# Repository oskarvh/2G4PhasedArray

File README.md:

# 2G4PhasedArray
Design files for a modular 2.4 GHz phased array antenna

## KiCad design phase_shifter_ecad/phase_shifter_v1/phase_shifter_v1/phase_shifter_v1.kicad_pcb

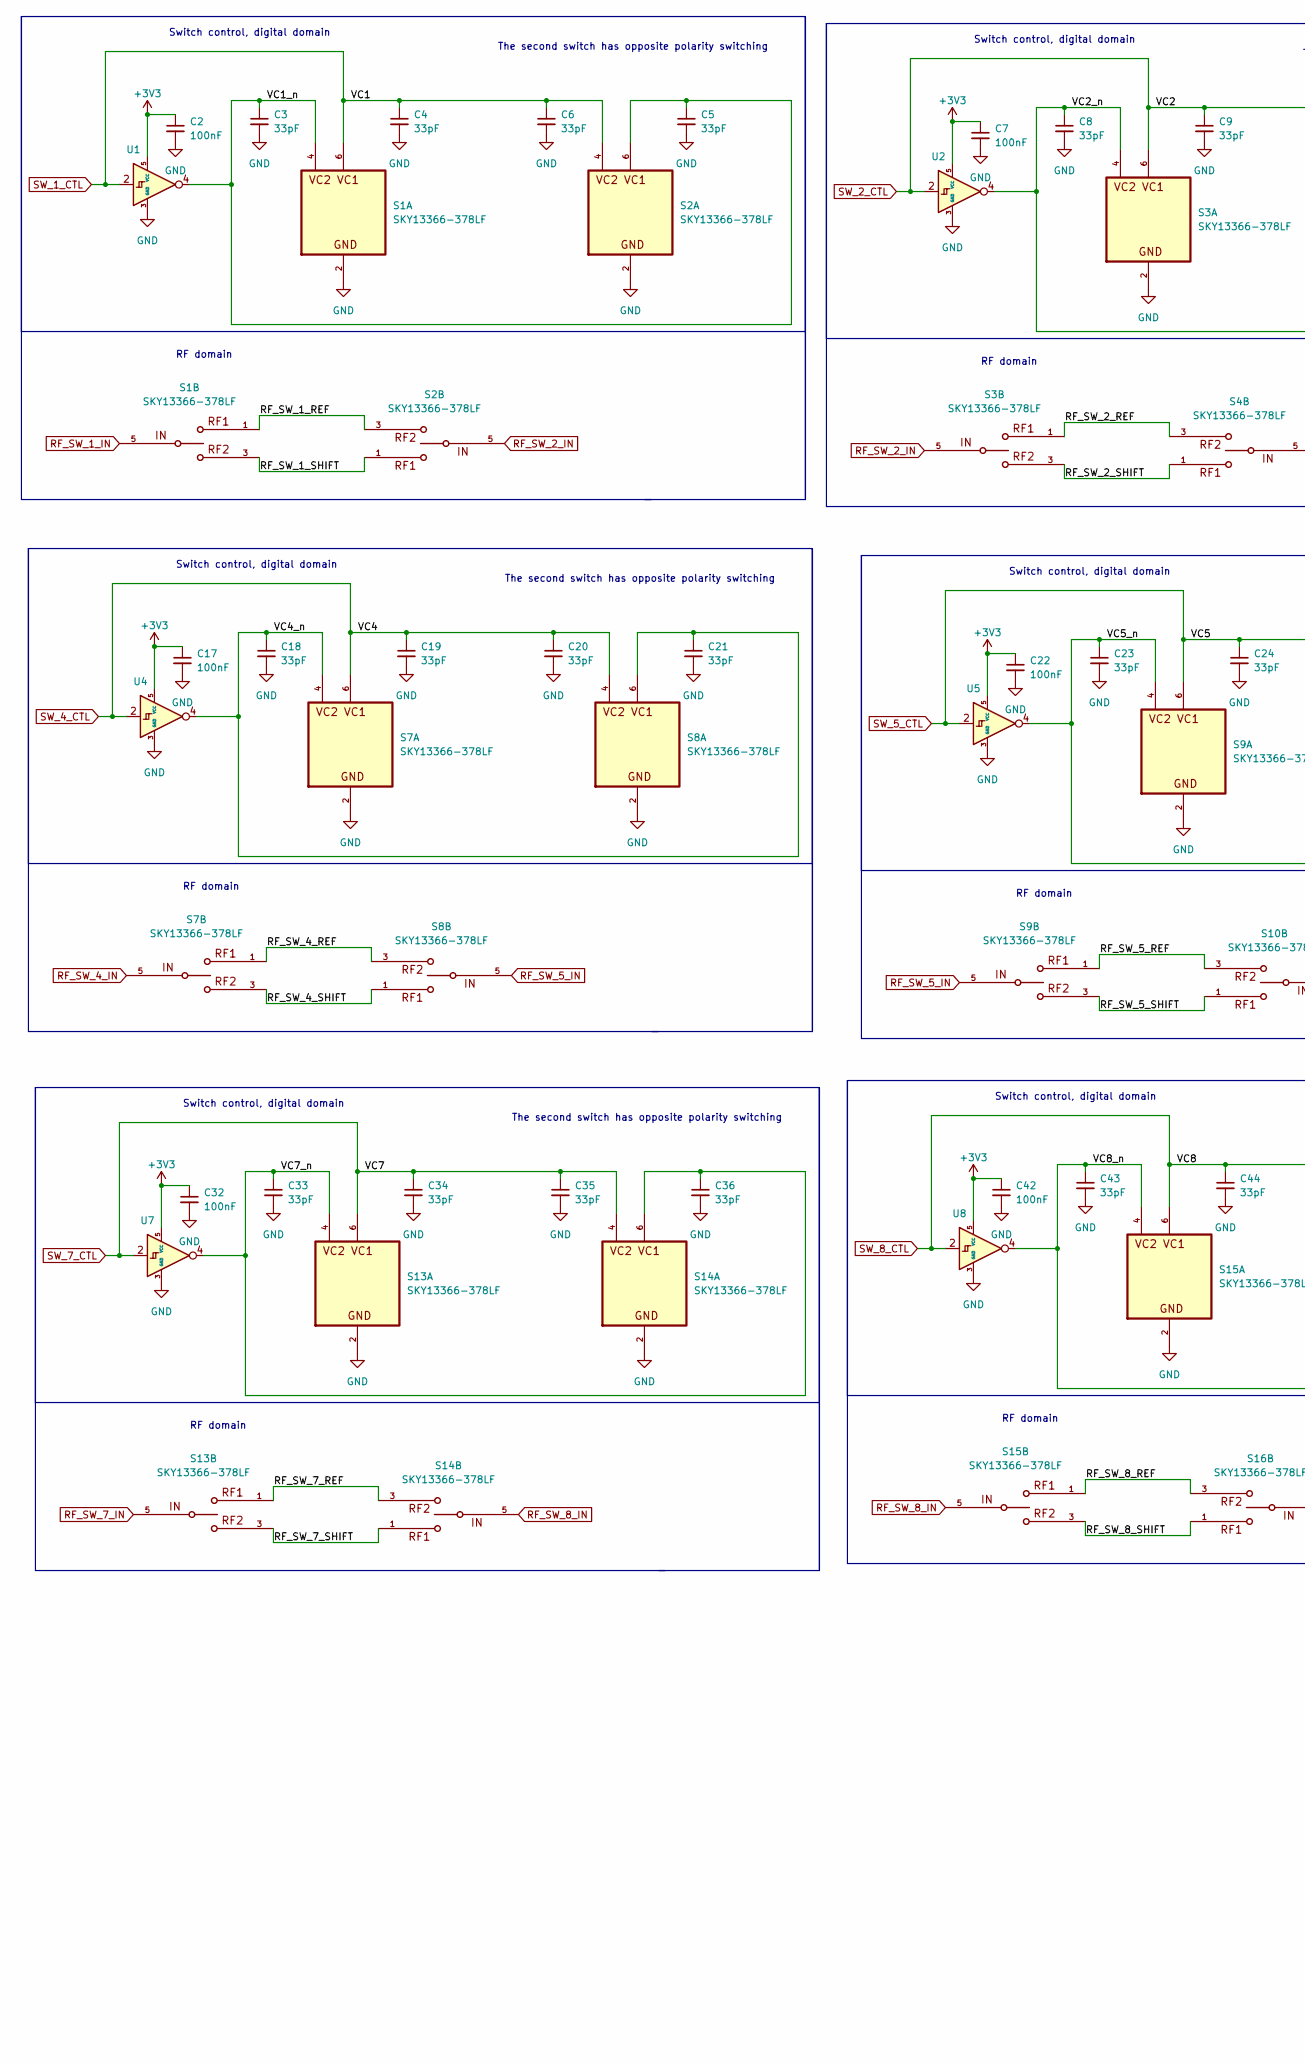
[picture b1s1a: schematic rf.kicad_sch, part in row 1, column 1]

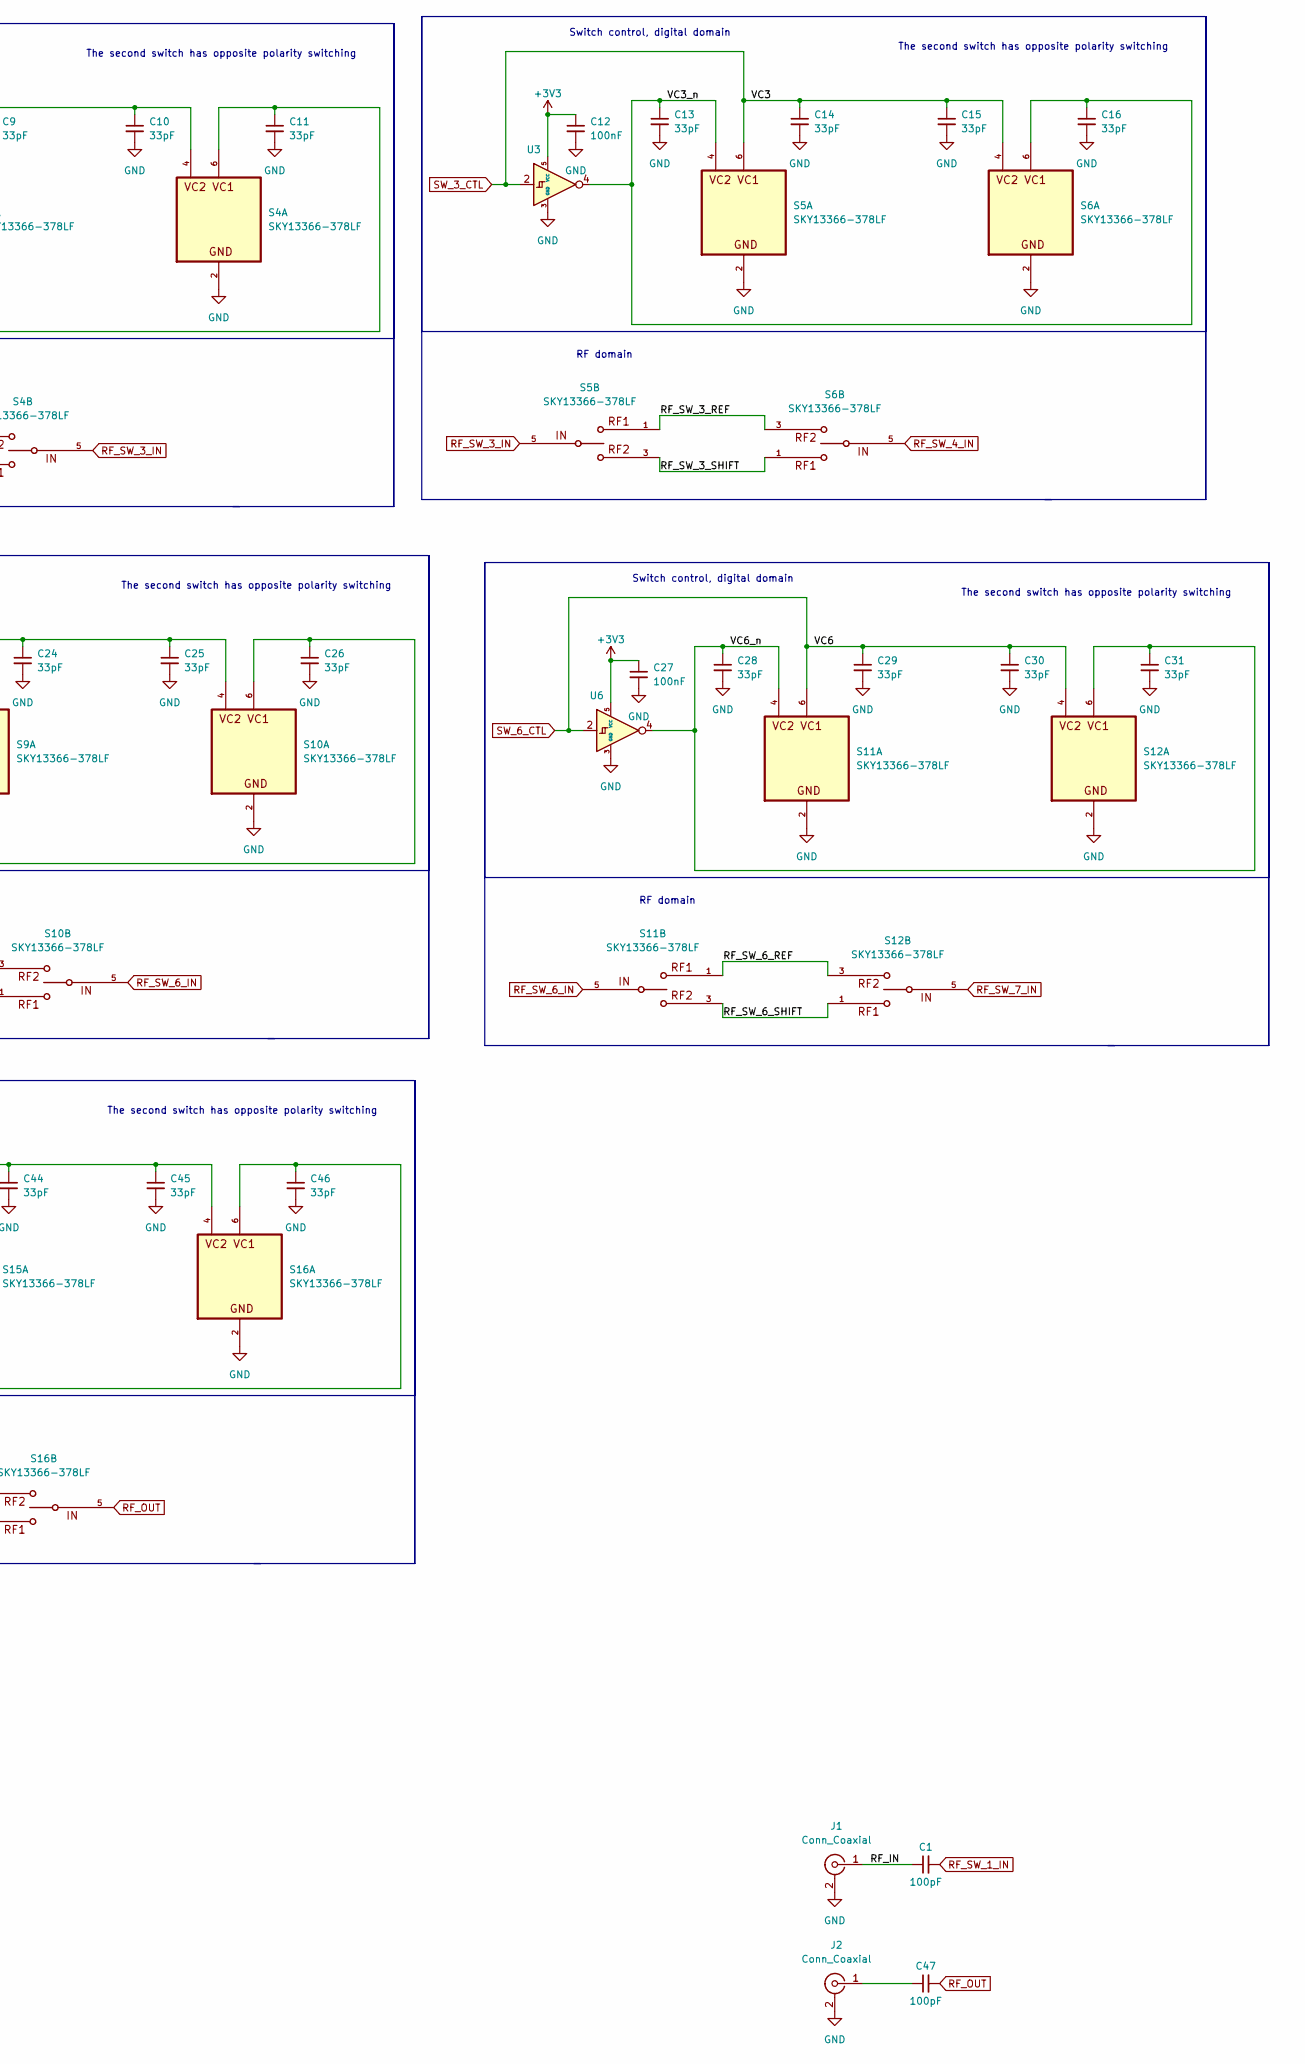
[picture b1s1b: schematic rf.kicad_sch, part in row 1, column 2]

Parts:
C1, C47: 100pF; C_0402_1005Metric
C2, C7, C12, C17, C22, C27, C32, C42: 100nF; C_0402_1005Metric
C3, C4, C5, C6, C8, C9, C10, C11, C13, C14, C15, C16, C18, C19, C20, C21, C23, C24, C25, C26, C28, C29, C30, C31, C33, C34, C35, C36, C43, C44, C45, C46: 33pF; C_0402_1005Metric
J1: Conn_Coaxial; SMA_Amphenol_132134-10_Vertical
J2: Conn_Coaxial; 919382J51P
S1, S2, S3, S4, S5, S6, S7, S8, S9, S10, S11, S12, S13, S14, S15, S16: SKY13366-378LF; QFN6-LF
U1, U2, U3, U4, U5, U6, U7, U8: SN74AUP1T04DCKR; SOT65P210X110-5N

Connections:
+3V3: C2.1, C7.1, C12.1, C17.1, C22.1, C27.1, C32.1, C42.1, U1.5 (VCC), U2.5 (VCC), U3.5 (VCC), U4.5 (VCC), U5.5 (VCC), U6.5 (VCC), U7.5 (VCC), U8.5 (VCC); also elsewhere on the board
/RF domain/RF_IN: C1.1, J1.1 (In)
/RF domain/RF_SW_1_REF: S1.1, S2.3
/RF domain/RF_SW_1_SHIFT: S1.3, S2.1
/RF domain/RF_SW_2_REF: S3.1, S4.3
/RF domain/RF_SW_2_SHIFT: S3.3, S4.1
/RF domain/RF_SW_3_REF: S5.1, S6.3
/RF domain/RF_SW_3_SHIFT: S5.3, S6.1
/RF domain/RF_SW_4_REF: S7.1, S8.3
/RF domain/RF_SW_4_SHIFT: S7.3, S8.1
/RF domain/RF_SW_5_REF: S9.1, S10.3
/RF domain/RF_SW_5_SHIFT: S9.3, S10.1
/RF domain/RF_SW_6_REF: S11.1, S12.3
/RF domain/RF_SW_6_SHIFT: S11.3, S12.1
/RF domain/RF_SW_7_REF: S13.1, S14.3
/RF domain/RF_SW_7_SHIFT: S13.3, S14.1
/RF domain/RF_SW_8_REF: S15.1, S16.3
/RF domain/RF_SW_8_SHIFT: S15.3, S16.1
/RF domain/VC1_n: C3.1, C5.1, S1.4, S2.6, U1.4
/RF domain/VC2_n: C8.1, C11.1, S3.4, S4.6, U2.4
/RF domain/VC3_n: C13.1, C16.1, S5.4, S6.6, U3.4
/RF domain/VC4_n: C18.1, C21.1, S7.4, S8.6, U4.4
/RF domain/VC5_n: C23.1, C26.1, S9.4, S10.6, U5.4
/RF domain/VC6_n: C28.1, C31.1, S11.4, S12.6, U6.4
/RF domain/VC7_n: C33.1, C36.1, S13.4, S14.6, U7.4
/RF domain/VC8_n: C43.1, C46.1, S15.4, S16.6, U8.4
GND: C2.2, C3.2, C4.2, C5.2, C6.2, C7.2, C8.2, C9.2, C10.2, C11.2, C12.2, C13.2, C14.2, C15.2, C16.2, C17.2, C18.2, C19.2, C20.2, C21.2, C22.2, C23.2, C24.2, C25.2, C26.2, C27.2, C28.2, C29.2, C30.2, C31.2, C32.2, C33.2, C34.2, C35.2, C36.2, C42.2, C43.2, C44.2, C45.2, C46.2, J1.2 (Ext), J2.2 (Ext), S1.2, S2.2, S3.2, S4.2, S5.2, S6.2, S7.2, S8.2, S9.2, S10.2, S11.2, S12.2, S13.2, S14.2, S15.2, S16.2, U1.3 (GND), U2.3 (GND), U3.3 (GND), U4.3 (GND), U5.3 (GND), U6.3 (GND), U7.3 (GND), U8.3 (GND); also elsewhere on the board
unnamed: C47.1, J2.1 (In)
RF_OUT: C47.2, S16.5
RF_SW_1_IN: C1.2, S1.5
RF_SW_2_IN: S2.5, S3.5
RF_SW_3_IN: S4.5, S5.5
RF_SW_4_IN: S6.5, S7.5
RF_SW_5_IN: S8.5, S9.5
RF_SW_6_IN: S10.5, S11.5
RF_SW_7_IN: S12.5, S13.5
RF_SW_8_IN: S14.5, S15.5
SW_1_CTL: C4.1, C6.1, S1.6, S2.4, U1.2; also elsewhere on the board
SW_2_CTL: C9.1, C10.1, S3.6, S4.4, U2.2; also elsewhere on the board
SW_3_CTL: C14.1, C15.1, S5.6, S6.4, U3.2; also elsewhere on the board
SW_4_CTL: C19.1, C20.1, S7.6, S8.4, U4.2; also elsewhere on the board
SW_5_CTL: C24.1, C25.1, S9.6, S10.4, U5.2; also elsewhere on the board
SW_6_CTL: C29.1, C30.1, S11.6, S12.4, U6.2; also elsewhere on the board
SW_7_CTL: C34.1, C35.1, S13.6, S14.4, U7.2; also elsewhere on the board
SW_8_CTL: C44.1, C45.1, S15.6, S16.4, U8.2; also elsewhere on the board

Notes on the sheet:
The second switch has opposite polarity switching
Switch control, digital domain
RF domain

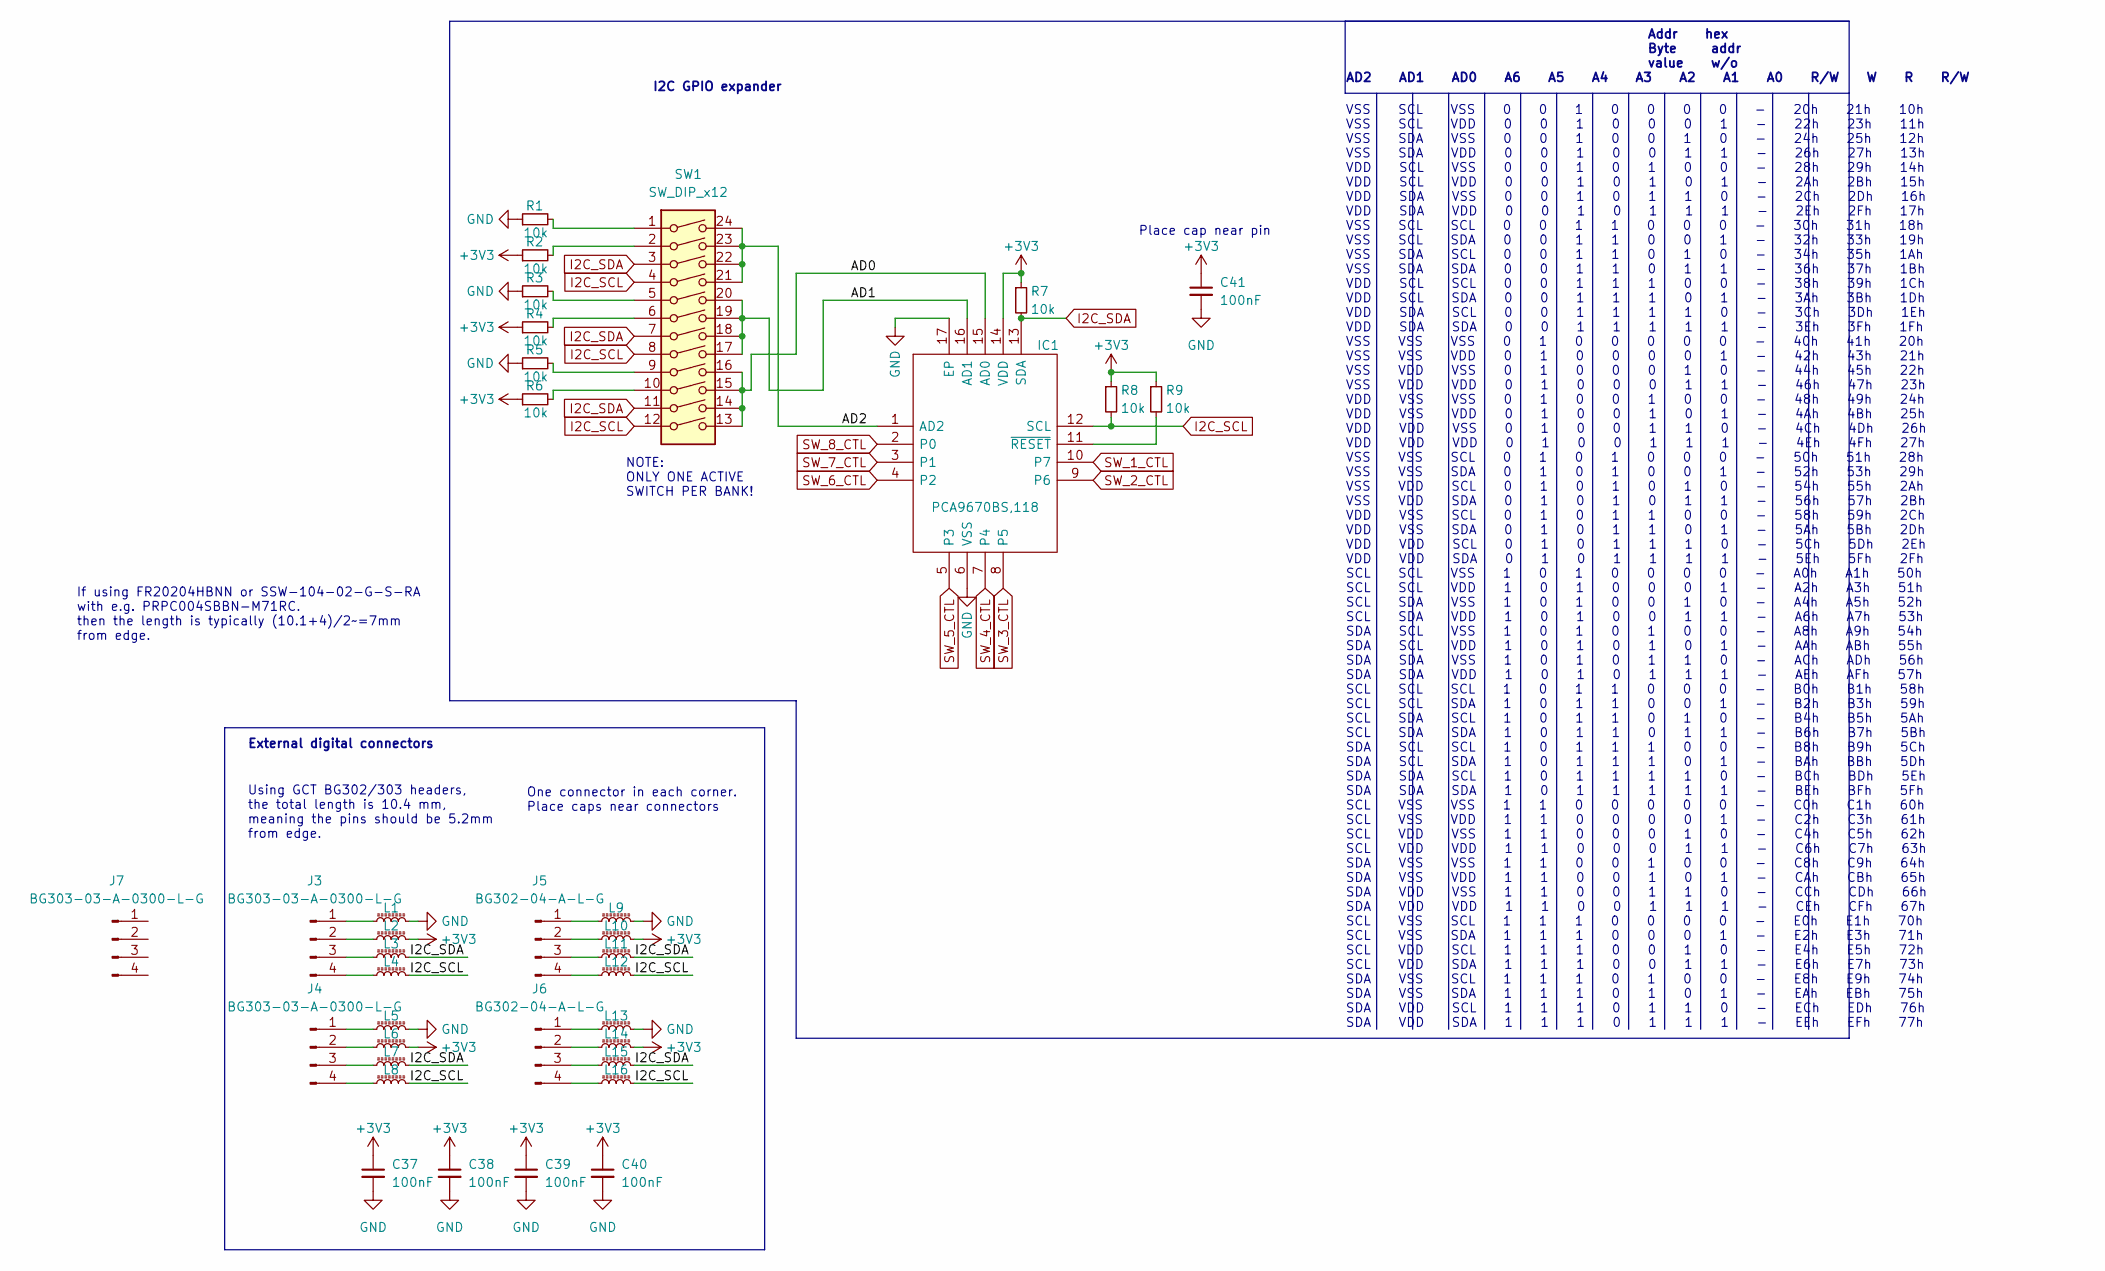
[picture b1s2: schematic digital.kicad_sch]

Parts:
C37, C38, C39, C40, C41: 100nF; C_0402_1005Metric
IC1: PCA9670BS,118; QFN50P300X300X100-17N-D; Mouser Part Number 771-PCA9670BS118
J3, J4: BG303-03-A-0300-L-G; PinHeader_1x04_P2.54mm_Vertical
J5, J6: BG302-04-A-L-G; PinHeader_1x04_P2.54mm_Vertical
J7: BG303-03-A-0300-L-G; PinSocket_1x04_P2.54mm_Horizontal
L1, L2, L3, L4, L5, L6, L7, L8, L9, L10, L11, L12, L13, L14, L15, L16: 36541E3N9JTDG; L_0402_1005Metric
R1, R2, R3, R4, R5, R6, R7, R8, R9: 10k; R_0402_1005Metric
SW1: SW_DIP_x12; 218-12LP_CTS

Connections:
+3V3: C37.1, C38.1, C39.1, C40.1, C41.1, IC1.14 (VDD), L2.2, L6.2, L10.2, L14.2, R2.1, R4.1, R6.1, R7.1, R8.1, R9.1; also elsewhere on the board
/Digital domain/AD0: IC1.15 (AD0), SW1.13, SW1.14, SW1.15, SW1.16
/Digital domain/AD1: IC1.16 (AD1), SW1.17, SW1.18, SW1.19, SW1.20
/Digital domain/AD2: IC1.1 (AD2), SW1.21, SW1.22, SW1.23, SW1.24
GND: C37.2, C38.2, C39.2, C40.2, C41.2, IC1.6 (VSS), IC1.17 (EP), L1.2, L5.2, L9.2, L13.2, R1.1, R3.1, R5.1; also elsewhere on the board
I2C_SCL: IC1.12 (SCL), L4.2, L8.2, L12.2, L16.2, R8.2, SW1.4, SW1.8, SW1.12
I2C_SDA: IC1.13 (SDA), L3.2, L7.2, L11.2, L15.2, R7.2, SW1.3, SW1.7, SW1.11
unnamed: IC1.11 (~RESET), R9.2
unnamed: J3.1, L1.1
unnamed: J3.2, L2.1
unnamed: J3.3, L3.1
unnamed: J3.4, L4.1
unnamed: J4.1, L5.1
unnamed: J4.2, L6.1
unnamed: J4.3, L7.1
unnamed: J4.4, L8.1
unnamed: J5.1, L9.1
unnamed: J5.2, L10.1
unnamed: J5.3, L11.1
unnamed: J5.4, L12.1
unnamed: J6.1, L13.1
unnamed: J6.2, L14.1
unnamed: J6.3, L15.1
unnamed: J6.4, L16.1
unnamed: R1.2, SW1.1
unnamed: R2.2, SW1.2
unnamed: R3.2, SW1.5
unnamed: R4.2, SW1.6
unnamed: R5.2, SW1.9
unnamed: R6.2, SW1.10
SW_1_CTL: IC1.10 (P7); also elsewhere on the board
SW_2_CTL: IC1.9 (P6); also elsewhere on the board
SW_3_CTL: IC1.8 (P5); also elsewhere on the board
SW_4_CTL: IC1.7 (P4); also elsewhere on the board
SW_5_CTL: IC1.5 (P3); also elsewhere on the board
SW_6_CTL: IC1.4 (P2); also elsewhere on the board
SW_7_CTL: IC1.3 (P1); also elsewhere on the board
SW_8_CTL: IC1.2 (P0); also elsewhere on the board

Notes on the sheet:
NOTE: ONLY ONE ACTIVE SWITCH PER BANK!
Using GCT BG302/303 headers, the total length is 10.4 mm, meaning the pins should be 5.2mm from edge.
I2C GPIO expander
One connector in each corner. Place caps near connectors
If using FR20204HBNN or SSW-104-02-G-S-RA with e.g. PRPC004SBBN-M71RC. then the length is typically (10.1+4)/2~=7mm from edge.
Addr hex Byte addr value w/o AD2 AD1 AD0 A6 A5 A4 A3 A2 A1 A0 R/W W R R/W
VSS SCL VSS 0 0 1 0 0 0 0 - 20h 21h 10h VSS SCL VDD 0 0 1 0 0 0 1 - 22h 23h 11h VSS SDA VSS 0 0 1 0 0 1 0 - 24h 25h 12h VSS SDA VDD 0 0 1 0 0 1 1 - 26h 27h 13h VDD SCL VSS 0 0 1 0 1 0 0 - 28h 29h 14h VDD SCL VDD 0 0 1 0 1 0 1 - 2Ah 2Bh 15h VDD SDA VSS 0 0 1 0 1 1 0 - 2Ch 2Dh 16h VDD SDA VDD 0 0 1 0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
Place cap near pin
External digital connectors

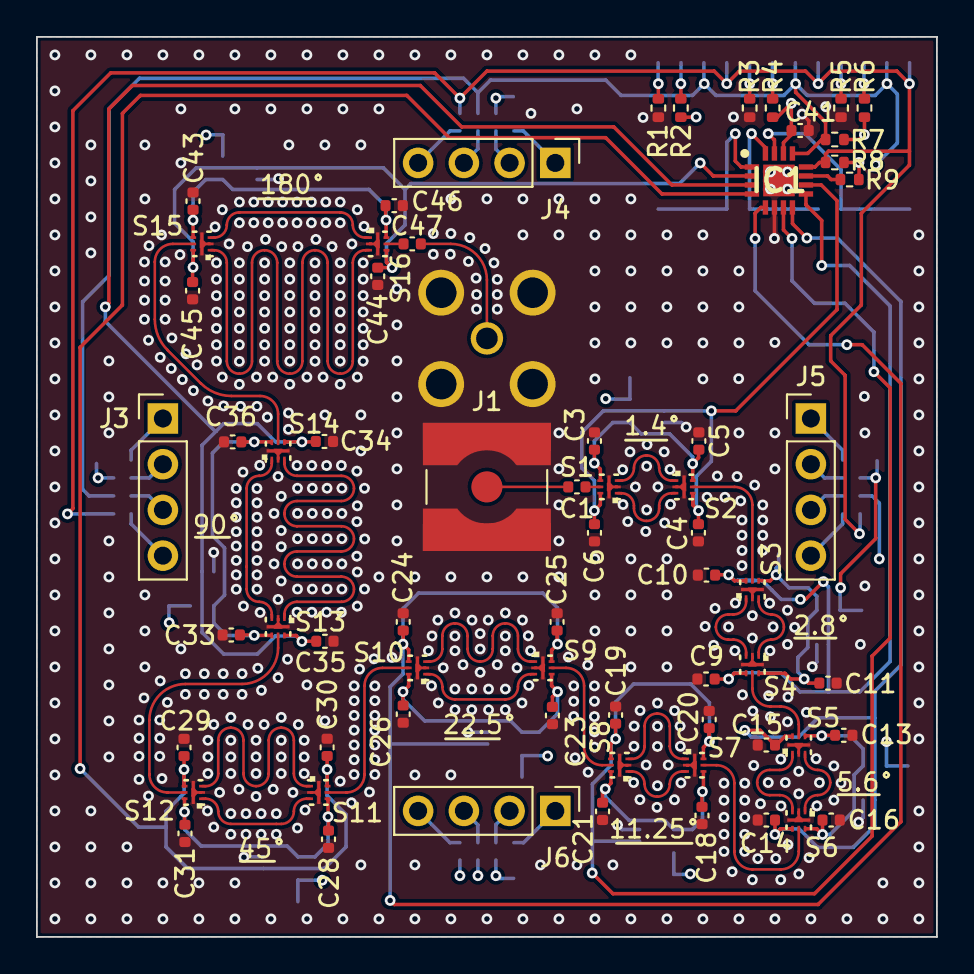
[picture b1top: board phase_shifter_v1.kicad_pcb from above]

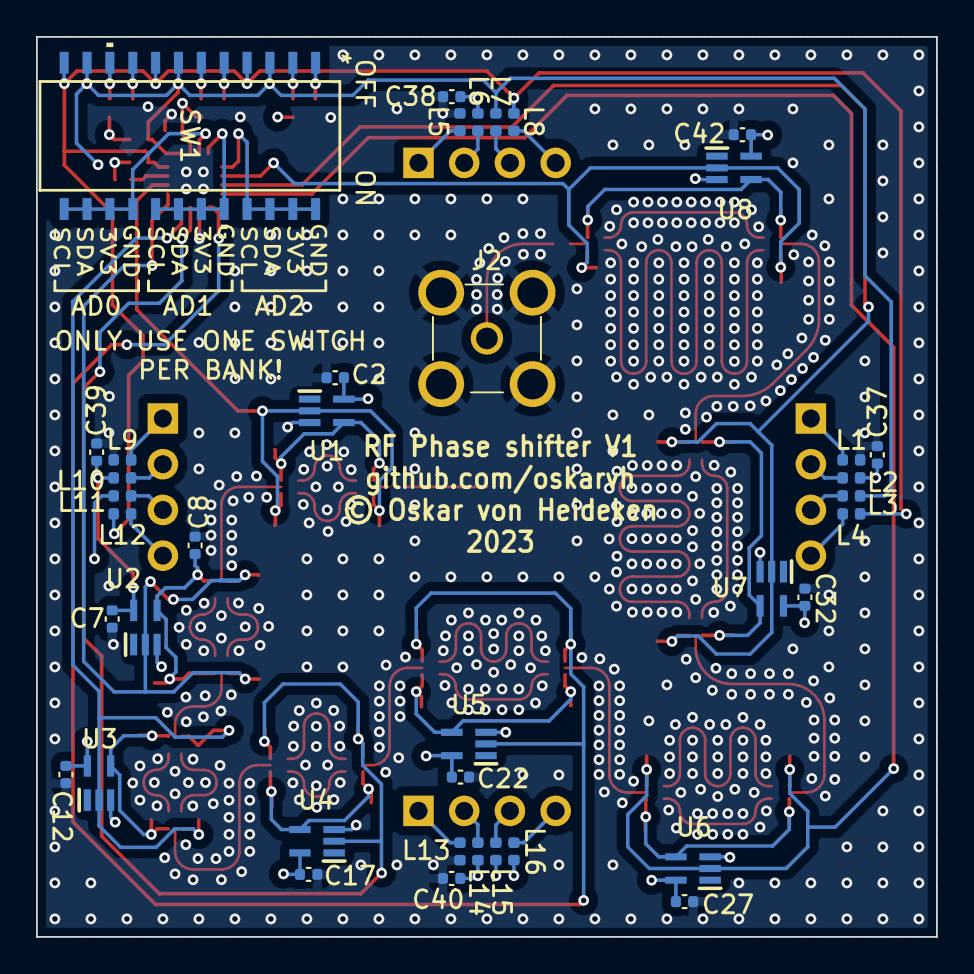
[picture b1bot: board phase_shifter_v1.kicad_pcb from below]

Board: 4 copper layers, 50.0 x 50.0 mm, 104 parts (39 on the bottom side), 73 nets.

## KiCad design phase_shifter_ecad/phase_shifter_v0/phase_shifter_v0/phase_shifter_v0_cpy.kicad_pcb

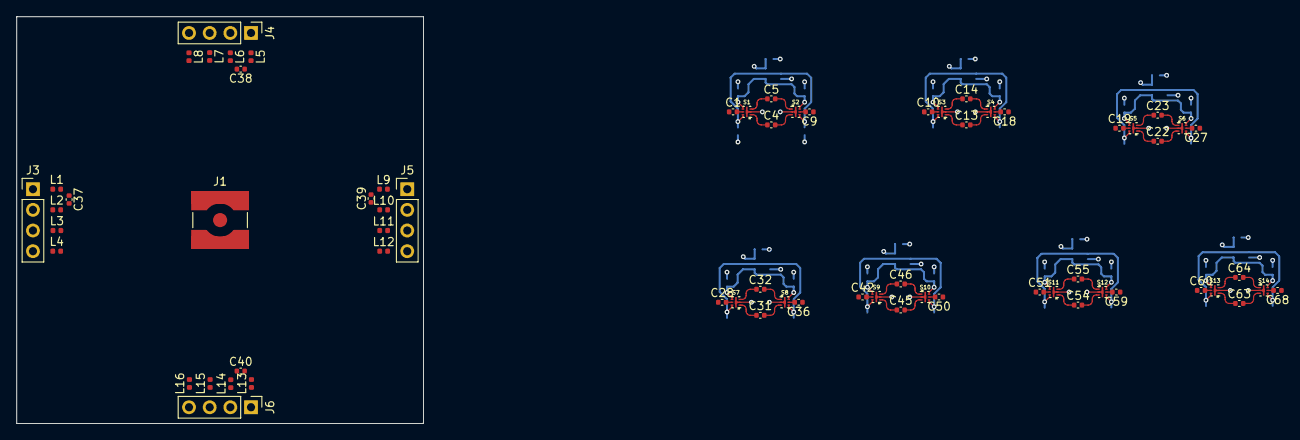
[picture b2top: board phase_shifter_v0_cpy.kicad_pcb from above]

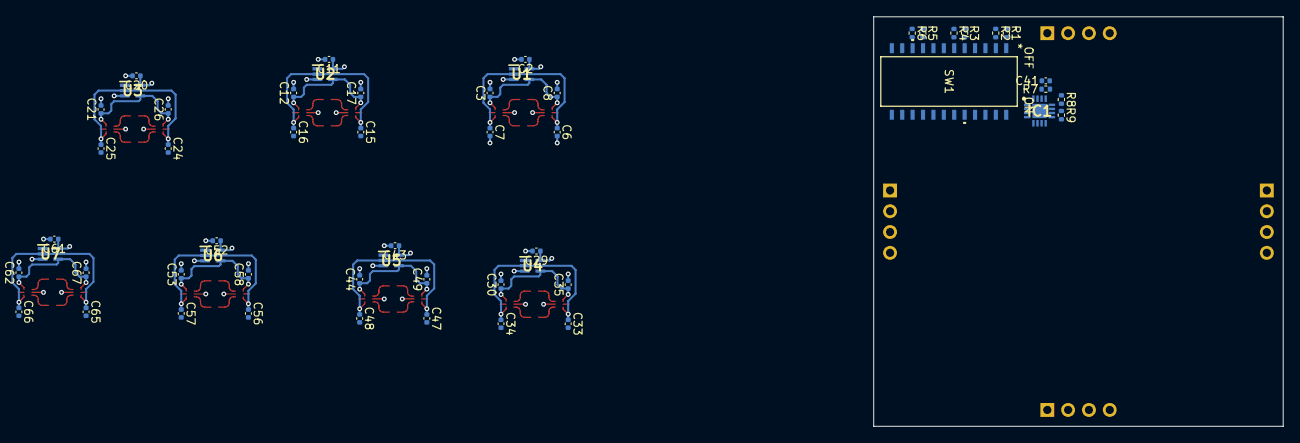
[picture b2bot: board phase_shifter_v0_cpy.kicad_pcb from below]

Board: 4 copper layers, 50.0 x 50.0 mm, 121 parts (54 on the bottom side), 82 nets.

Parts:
C1, C4, C5, C9, C10, C13, C14, C18, C19, C22, C23, C27, C28, C31, C32, C36, C42, C45, C46, C50, C51, C54, C55, C59, C60, C63, C64, C68: 100pF; C_0402_1005Metric
C2, C11, C20, C29, C37, C38, C39, C40, C41, C43, C52, C61: 100nF; C_0402_1005Metric
C3, C6, C7, C8, C12, C15, C16, C17, C21, C24, C25, C26, C30, C33, C34, C35, C44, C47, C48, C49, C53, C56, C57, C58, C62, C65, C66, C67: 33pF; C_0402_1005Metric
IC1: PCA9670BS,118; QFN50P300X300X100-17N-D
J1: Conn_Coaxial; SMA_Amphenol_132134-10_Vertical
J3, J4, J5, J6: Conn_01x04_Male; PinHeader_1x04_P2.54mm_Vertical
L1, L2, L3, L4, L5, L6, L7, L8, L9, L10, L11, L12, L13, L14, L15, L16: 36541E3N9JTDG; L_0402_1005Metric
R1, R2, R3, R4, R5, R6, R7, R8, R9: 10k; R_0402_1005Metric
S1, S2, S3, S4, S5, S6, S7, S8, S9, S10, S11, S12, S13, S14: SKY13366-378LF; QFN6-LF
SW1: SW_DIP_x12; 218-12LP_CTS
U1, U2, U3, U4, U5, U6, U7: SN74AUP1T04DCKR; SOT65P210X110-5N

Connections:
+3V3: C2.1, C11.1, C20.1, C29.1, C37.1, C38.1, C39.1, C40.1, C41.1, C43.1, C52.1, C61.1, IC1.14 (VDD), L2.2, L6.2, L10.2, L14.2, R2.1, R4.1, R6.1, R7.1, R8.1, R9.1, U1.5 (VCC), U2.5 (VCC), U3.5 (VCC), U4.5 (VCC), U5.5 (VCC), U6.5 (VCC), U7.5 (VCC)
/digital domain/AD0: IC1.15 (AD0), SW1.21, SW1.22, SW1.23, SW1.24
/digital domain/AD1: IC1.16 (AD1), SW1.17, SW1.18, SW1.19, SW1.20
/digital domain/AD2: IC1.1 (AD2), SW1.13, SW1.14, SW1.15, SW1.16
/rf_domain/switch_design1/RF_SW_1_C: C10.2, S3.5
/rf_domain/switch_design1/RF_SW_1_OUT_C_1: C13.1, S3.1
/rf_domain/switch_design1/RF_SW_1_OUT_C_2: C14.1, S3.3
/rf_domain/switch_design1/RF_SW_2_C: C18.2, S4.5
/rf_domain/switch_design1/RF_SW_2_IN_C_1: C14.2, S4.1
/rf_domain/switch_design1/RF_SW_2_IN_C_2: C13.2, S4.3
/rf_domain/switch_design1/VC_n: C12.1, C17.1, S3.4, S4.6, U2.4
/rf_domain/switch_design2/RF_SW_1_C: C19.2, S5.5
/rf_domain/switch_design2/RF_SW_1_OUT_C_1: C22.1, S5.1
/rf_domain/switch_design2/RF_SW_1_OUT_C_2: C23.1, S5.3
/rf_domain/switch_design2/RF_SW_2_C: C27.2, S6.5
/rf_domain/switch_design2/RF_SW_2_IN_C_1: C23.2, S6.1
/rf_domain/switch_design2/RF_SW_2_IN_C_2: C22.2, S6.3
/rf_domain/switch_design2/VC_n: C21.1, C26.1, S5.4, S6.6, U3.4
/rf_domain/switch_design3/RF_SW_1_C: C28.2, S7.5
/rf_domain/switch_design3/RF_SW_1_OUT_C_1: C31.1, S7.1
/rf_domain/switch_design3/RF_SW_1_OUT_C_2: C32.1, S7.3
/rf_domain/switch_design3/RF_SW_2_C: C36.2, S8.5
/rf_domain/switch_design3/RF_SW_2_IN_C_1: C32.2, S8.1
/rf_domain/switch_design3/RF_SW_2_IN_C_2: C31.2, S8.3
/rf_domain/switch_design3/VC_n: C30.1, C35.1, S7.4, S8.6, U4.4
/rf_domain/switch_design4/RF_SW_1_C: C42.2, S9.5
/rf_domain/switch_design4/RF_SW_1_OUT_C_1: C45.1, S9.1
/rf_domain/switch_design4/RF_SW_1_OUT_C_2: C46.1, S9.3
/rf_domain/switch_design4/RF_SW_2_C: C50.2, S10.5
/rf_domain/switch_design4/RF_SW_2_IN_C_1: C46.2, S10.1
/rf_domain/switch_design4/RF_SW_2_IN_C_2: C45.2, S10.3
/rf_domain/switch_design4/VC_n: C44.1, C49.1, S9.4, S10.6, U5.4
/rf_domain/switch_design5/RF_SW_1_C: C51.2, S11.5
/rf_domain/switch_design5/RF_SW_1_OUT_C_1: C54.1, S11.1
/rf_domain/switch_design5/RF_SW_1_OUT_C_2: C55.1, S11.3
/rf_domain/switch_design5/RF_SW_2_C: C59.2, S12.5
/rf_domain/switch_design5/RF_SW_2_IN_C_1: C55.2, S12.1
/rf_domain/switch_design5/RF_SW_2_IN_C_2: C54.2, S12.3
/rf_domain/switch_design5/VC_n: C53.1, C58.1, S11.4, S12.6, U6.4
/rf_domain/switch_design6/RF_SW_1_C: C60.2, S13.5
/rf_domain/switch_design6/RF_SW_1_OUT_C_1: C63.1, S13.1
/rf_domain/switch_design6/RF_SW_1_OUT_C_2: C64.1, S13.3
/rf_domain/switch_design6/RF_SW_2_C: C68.2, S14.5
/rf_domain/switch_design6/RF_SW_2_IN_C_1: C64.2, S14.1
/rf_domain/switch_design6/RF_SW_2_IN_C_2: C63.2, S14.3
/rf_domain/switch_design6/VC_n: C62.1, C67.1, S13.4, S14.6, U7.4
/rf_domain/switch_design/RF_SW_1_C: C1.2, S1.5
/rf_domain/switch_design/RF_SW_1_OUT_C_1: C4.1, S1.1
/rf_domain/switch_design/RF_SW_1_OUT_C_2: C5.1, S1.3
/rf_domain/switch_design/RF_SW_2_C: C9.2, S2.5
/rf_domain/switch_design/RF_SW_2_IN_C_1: C5.2, S2.1
/rf_domain/switch_design/RF_SW_2_IN_C_2: C4.2, S2.3
/rf_domain/switch_design/VC_n: C3.1, C8.1, S1.4, S2.6, U1.4
GND: C2.2, C3.2, C6.2, C7.2, C8.2, C11.2, C12.2, C15.2, C16.2, C17.2, C20.2, C21.2, C24.2, C25.2, C26.2, C29.2, C30.2, C33.2, C34.2, C35.2, C37.2, C38.2, C39.2, C40.2, C41.2, C43.2, C44.2, C47.2, C48.2, C49.2, C52.2, C53.2, C56.2, C57.2, C58.2, C61.2, C62.2, C65.2, C66.2, C67.2, IC1.6 (VSS), IC1.17 (EP), J1.2 (Ext), L1.2, L5.2, L9.2, L13.2, R1.1, R3.1, R5.1, S1.2, S2.2, S3.2, S4.2, S5.2, S6.2, S7.2, S8.2, S9.2, S10.2, S11.2, S12.2, S13.2, S14.2, U1.3 (GND), U2.3 (GND), U3.3 (GND), U4.3 (GND), U5.3 (GND), U6.3 (GND), U7.3 (GND)
I2C_SCL: IC1.12 (SCL), L4.2, L8.2, L12.2, L16.2, R8.2, SW1.4, SW1.8, SW1.12
I2C_SDA: IC1.13 (SDA), L3.2, L7.2, L11.2, L15.2, R7.2, SW1.3, SW1.7, SW1.11
unnamed: IC1.11 (~RESET), R9.2
unnamed: J3.1, L1.1
unnamed: J3.2, L2.1
unnamed: J3.3, L3.1
unnamed: J3.4, L4.1
unnamed: J4.1, L5.1
unnamed: J4.2, L6.1
unnamed: J4.3, L7.1
unnamed: J4.4, L8.1
unnamed: J5.1, L9.1
unnamed: J5.2, L10.1
unnamed: J5.3, L11.1
unnamed: J5.4, L12.1
unnamed: J6.1, L13.1
unnamed: J6.2, L14.1
unnamed: J6.3, L15.1
unnamed: J6.4, L16.1
unnamed: R1.2, SW1.1
unnamed: R2.2, SW1.2
unnamed: R3.2, SW1.5
unnamed: R4.2, SW1.6
unnamed: R5.2, SW1.9
unnamed: R6.2, SW1.10
RF_SW_1_IN: C1.1, C10.1, C19.1, C28.1, C42.1, C51.1, C60.1, J1.1 (In)
RF_SW_2_OUT: C9.1, C18.1, C27.1, C36.1, C50.1, C59.1, C68.1
SW_1_CTL: C6.1, C7.1, C15.1, C16.1, C24.1, C25.1, C33.1, C34.1, C47.1, C48.1, C56.1, C57.1, C65.1, C66.1, S1.6, S2.4, S3.6, S4.4, S5.6, S6.4, S7.6, S8.4, S9.6, S10.4, S11.6, S12.4, S13.6, S14.4, U1.2, U2.2, U3.2, U4.2, U5.2, U6.2, U7.2

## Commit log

2023-10-16 Added design files.
2023-11-24 rev0 of antenna and phase shifter done

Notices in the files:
phase_shifter_ecad/phase_shifter_v1/phase_shifter_v1/phase_shifter_v1.kicad_pcb:
© Oskar von Heideken
